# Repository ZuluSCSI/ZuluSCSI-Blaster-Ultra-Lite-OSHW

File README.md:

ZuluSCSI® Blaster Ultra Lite OSHW
================

This repository contains the KiCAD 10 schematic and PCB design files for an Open Source Hardware variant of the RP2350B-based ZuluSCSI® Blaster 

ZuluSCSI® Ultra Lite OSHW is the worlds first* **_open-source**_ [OSHWA-certified](https://certification.oshwa.org/us002873.html) _Ultra_ SCSI emulator, an open-source alternative to our commercially available ZuluSCSI Blaster, designed with cost efficiency in mind.

ZuluSCSI® Blaster Ultra Lite runs unmodified [ZuluSCSI Blaster firmware](https://github.com/ZuluSCSI/ZuluSCSI-firmware/releases)

Pre-prepared gerbers and BoM files are available in [the release section](https://github.com/ZuluSCSI/ZuluSCSI-Blaster-Ultra-Lite-OSHW/releases/tag/Rev2026b)

License
----------------------------

This hardware design is licensed under the terms of the [strongly reciprocal CERN OHL-S V2 license](https://ohwr.org/cern_ohl_s_v2.txt) 

ZuluSCSI® is a registered trademark of Rabbit Hole Computing, and may not be used commercially without the express written consent of Rabbit Hole Computing. Individuals producing ZuluSCSI boards for personal use are hereby granted permission to use the ZuluSCSI trademark in a noncommercial capacity.

_Any_ use of the ZuluSCSI® [registered trademark](https://tmsearch.uspto.gov/search/search-results/97574699) in a **commercial** context requires **prior written consent from Rabbit Hole Computing.**

*That we know of :)

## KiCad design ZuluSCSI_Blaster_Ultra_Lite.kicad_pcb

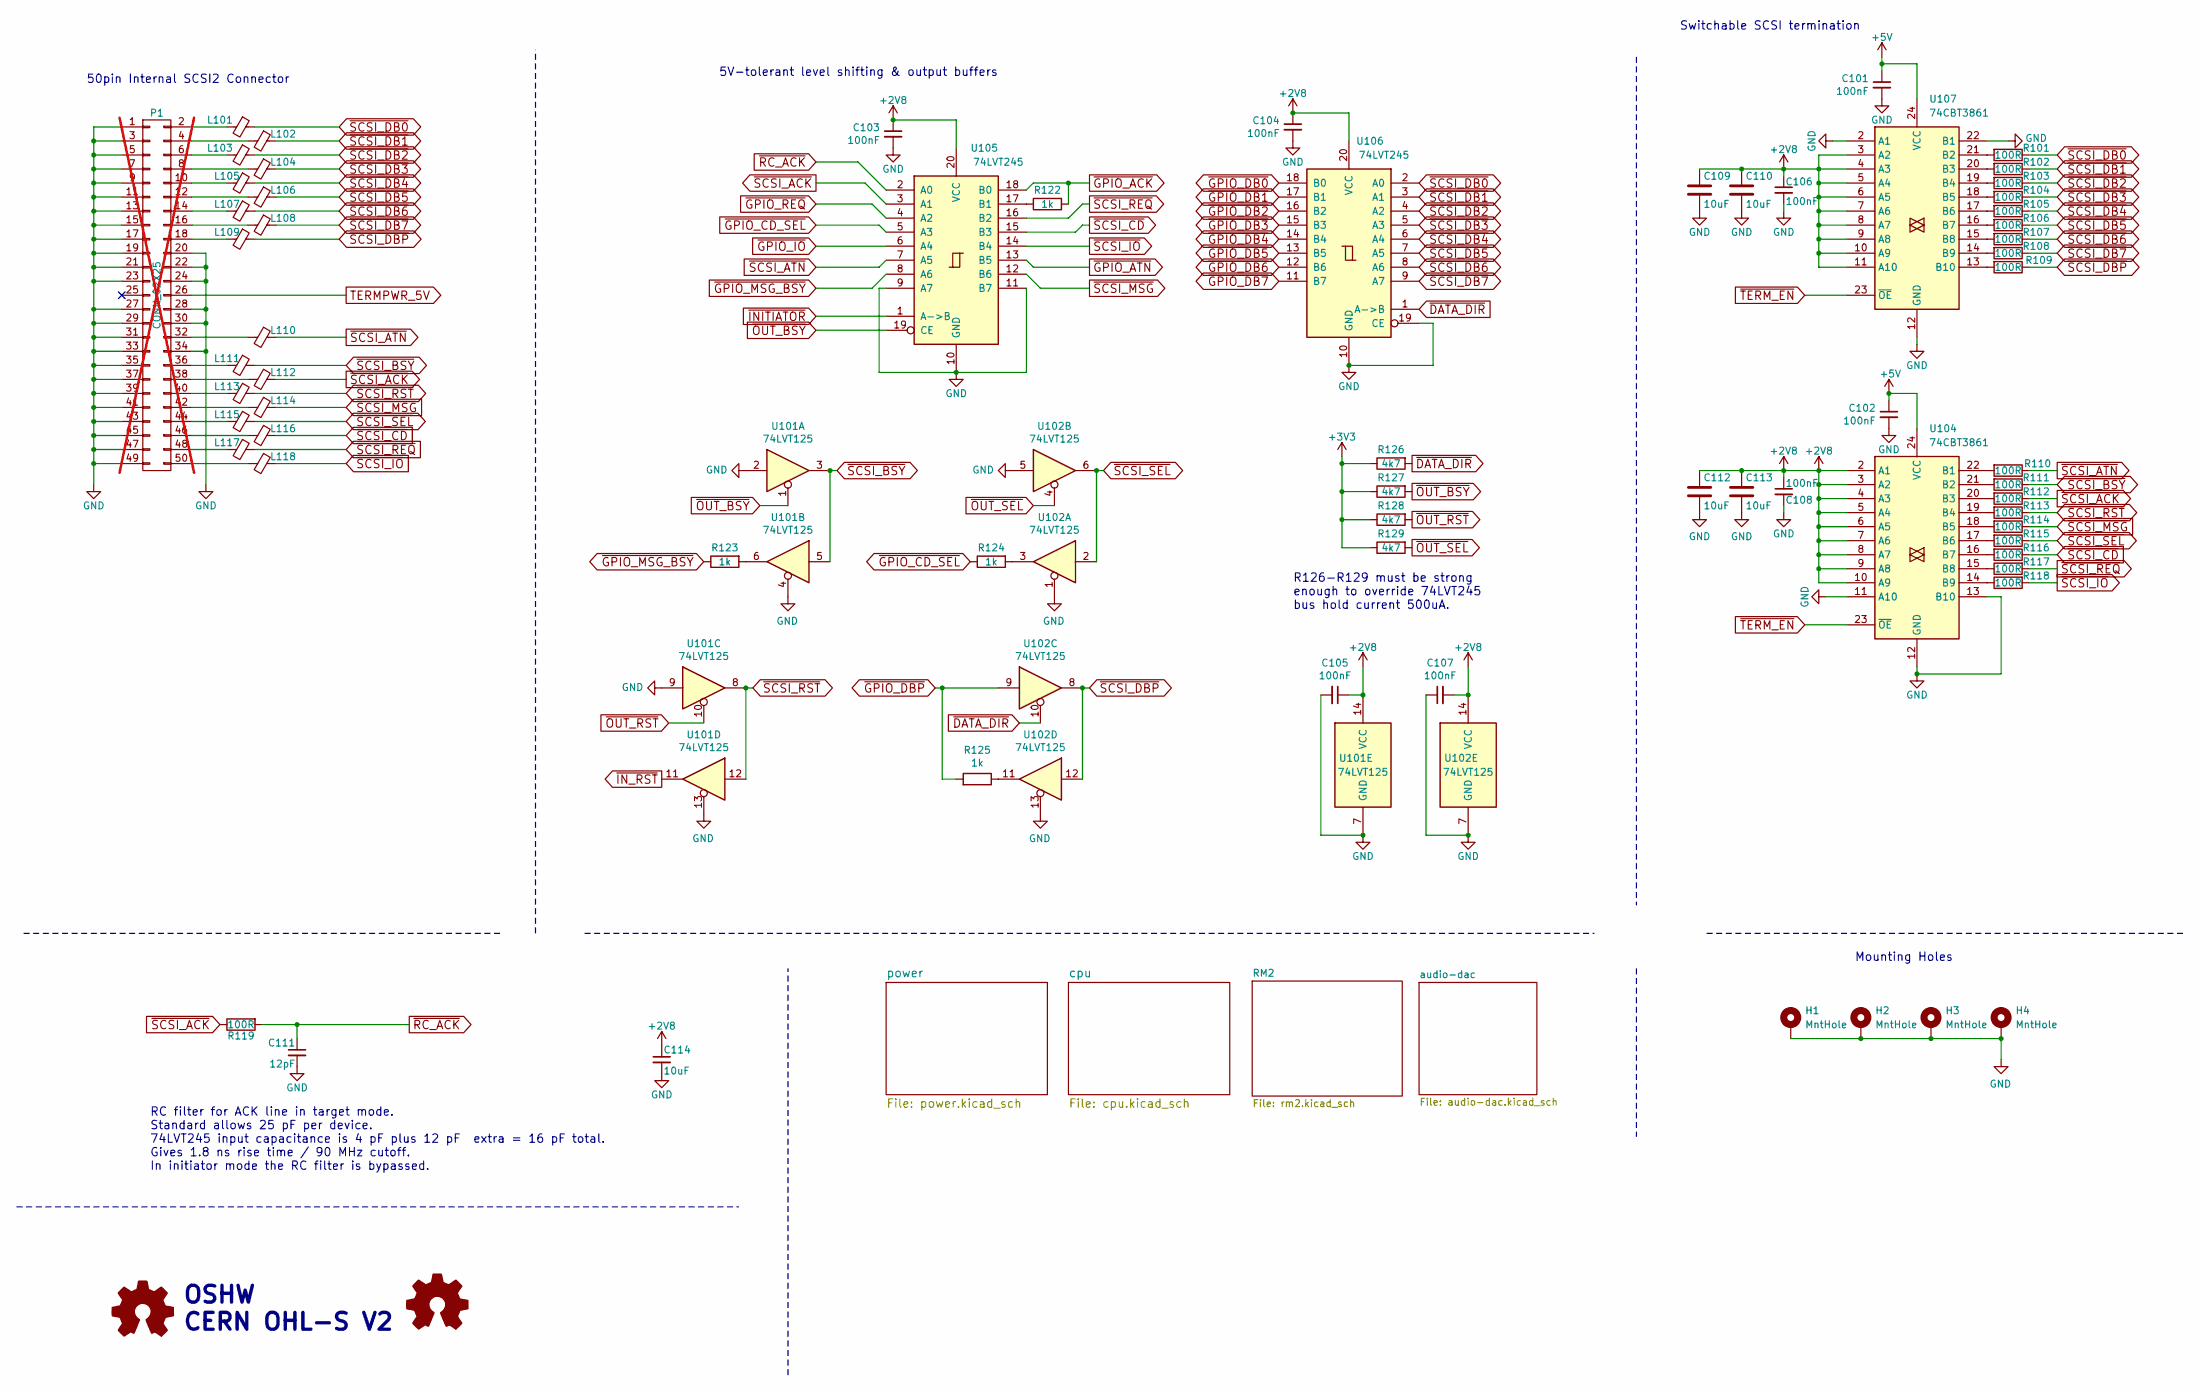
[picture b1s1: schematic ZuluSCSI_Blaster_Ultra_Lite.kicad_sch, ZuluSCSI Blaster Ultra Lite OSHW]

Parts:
C101, C102, C103, C104, C105, C106, C107, C108: 100nF; C_0402_1005Metric; PartNumber CL05B104KO5NNNC; LCSC C1525
C109, C110, C112, C113: 10uF; C_0805_2012Metric; Voltage Rating 16V; PartNumber CL21A106KAYNNNE; LCSC C15850
C111: 12pF; C_0603_1608Metric; PartNumber C0603C120J5GAC7867; LCSC C38523
C114: 10uF; C_0805_2012Metric; PartNumber CL21A106KAYNNNE; LCSC C15850
H1, H2, H3, H4: MntHole; Screw_Hole_M3
L101, L102, L103, L104, L105, L106, L107, L108, L109, L110, L111, L112, L113, L114, L115, L116, L117, L118: Ferrite_Bead_Small; L_0603_1608Metric; PartNumber BLM18PG330SN1D; LCSC C88984
P1: CONN_02X25; IDC-Header_2x25_P2.54mm_Horizontal; PartNumber SBH11-PBPC-D25-RA-BK; LCSC C19193830; not fitted
R101, R102, R103, R104, R105, R106, R107, R108, R109, R110, R111, R112, R113, R114, R115, R116, R117, R118, R119: 100R; R_0603_1608Metric; PartNumber RC0603FR-07100RL; LCSC C22775
R122, R123, R124, R125: 1k; R_0603_1608Metric; PartNumber RC0603JR-071KL; LCSC C21190
R126, R127, R128, R129: 4k7; R_0603_1608Metric; PartNumber RC0603JR-074K7L; LCSC C23162
SYM1, SYM2: Logo_Open_Hardware_Small; OSHW-Logo_5.7x6mm_Copper_SolderMask
U101, U102: 74LVT125; SSOP_TSSOP-14_4.4x5mm_Pitch0.65mm_PCBWay-MaskClearance0.22mm; PartNumber SN74LVT125PWR; LCSC C7042
U104, U107: 74CBT3861; TSSOP-24_4.4x7.8mm_P0.65mm; PartNumber SN74CBT3861PWR; JLCPCBCORRECT 0;0;-90
U105, U106: 74LVT245; SSOP_TSSOP-20_5.3x7.2mm_P0.65mm; PartNumber SN74LVTH245APWR; LCSC C2652121

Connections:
+2V8: C103.1, C104.1, C105.1, C106.1, C107.2, C108.1, C109.1, C110.1, C112.1, C113.1, C114.1, U101.14 (VCC), U102.14 (VCC), U104.2 (A1), U104.3 (A2), U104.4 (A3), U104.5 (A4), U104.6 (A5), U104.7 (A6), U104.8 (A7), U104.9 (A8), U104.10 (A9), U105.20 (VCC), U106.20 (VCC), U107.3 (A2), U107.4 (A3), U107.5 (A4), U107.6 (A5), U107.7 (A6), U107.8 (A7), U107.9 (A8), U107.10 (A9), U107.11 (A10); also elsewhere on the board
+3V3: R126.1, R127.1, R128.1, R129.1; also elsewhere on the board
+5V: C101.1, C102.1, U104.24 (VCC), U107.24 (VCC); also elsewhere on the board
GND: C101.2, C102.2, C103.2, C104.2, C105.2, C106.2, C107.1, C108.2, C109.2, C110.2, C111.2, C112.2, C113.2, C114.2, H1.1 (1_1), H2.1 (1_1), H3.1 (1_1), H4.1 (1_1), P1.1, P1.3, P1.5, P1.7, P1.9, P1.11, P1.13, P1.15, P1.17, P1.19, P1.20, P1.21, P1.22, P1.23, P1.24, P1.27, P1.28, P1.29, P1.30, P1.31, P1.33, P1.34, P1.35, P1.37, P1.39, P1.41, P1.43, P1.45, P1.47, P1.49, U101.2, U101.4, U101.7 (GND), U101.9, U101.13, U102.1, U102.5, U102.7 (GND), U102.13, U104.11 (A10), U104.12 (GND), U104.13 (B10), U105.9 (A7), U105.10 (GND), U105.11 (B7), U106.10 (GND), U106.19 (CE), U107.2 (A1), U107.12 (GND), U107.22 (B1); also elsewhere on the board
unnamed: L101.2, P1.2
unnamed: L102.2, P1.4
unnamed: L103.2, P1.6
unnamed: L104.2, P1.8
unnamed: L105.2, P1.10
unnamed: L106.2, P1.12
unnamed: L107.2, P1.14
unnamed: L108.2, P1.16
unnamed: L109.2, P1.18
unnamed: L110.2, P1.32
unnamed: L111.2, P1.36
unnamed: L112.2, P1.38
unnamed: L113.2, P1.40
unnamed: L114.2, P1.42
unnamed: L115.2, P1.44
unnamed: L116.2, P1.46
unnamed: L117.2, P1.48
unnamed: L118.2, P1.50
unnamed: R123.2, U101.6
unnamed: R124.2, U102.3
unnamed: R125.1, U102.11
unnamed: R110.2, U104.22 (B1)
unnamed: R111.2, U104.21 (B2)
unnamed: R112.2, U104.20 (B3)
unnamed: R113.2, U104.19 (B4)
unnamed: R114.2, U104.18 (B5)
unnamed: R115.2, U104.17 (B6)
unnamed: R116.2, U104.16 (B7)
unnamed: R117.1, U104.15 (B8)
unnamed: R118.1, U104.14 (B9)
unnamed: R122.1, U105.17 (B1)
unnamed: R101.2, U107.21 (B2)
unnamed: R102.2, U107.20 (B3)
unnamed: R103.2, U107.19 (B4)
unnamed: R104.2, U107.18 (B5)
unnamed: R105.2, U107.17 (B6)
unnamed: R106.2, U107.16 (B7)
unnamed: R107.2, U107.15 (B8)
unnamed: R108.2, U107.14 (B9)
unnamed: R109.2, U107.13 (B10)
TERMPWR_5V: P1.26; also elsewhere on the board
~DATA_DIR: R126.2, U102.10, U106.1 (A->B); also elsewhere on the board
~GPIO_ACK: R122.2, U105.18 (B0); also elsewhere on the board
~GPIO_ATN: U105.13 (B5); also elsewhere on the board
~GPIO_CD_SEL: R124.1, U105.5 (A3); also elsewhere on the board
~GPIO_DB0: U106.18 (B0); also elsewhere on the board
~GPIO_DB1: U106.17 (B1); also elsewhere on the board
~GPIO_DB2: U106.16 (B2); also elsewhere on the board
~GPIO_DB3: U106.15 (B3); also elsewhere on the board
~GPIO_DB4: U106.14 (B4); also elsewhere on the board
~GPIO_DB5: U106.13 (B5); also elsewhere on the board
~GPIO_DB6: U106.12 (B6); also elsewhere on the board
~GPIO_DB7: U106.11 (B7); also elsewhere on the board
~GPIO_DBP: R125.2, U102.9; also elsewhere on the board
~GPIO_IO: U105.6 (A4); also elsewhere on the board
~GPIO_MSG_BSY: R123.1, U105.8 (A6); also elsewhere on the board
~GPIO_REQ: U105.4 (A2); also elsewhere on the board
~INITIATOR: U105.1 (A->B); also elsewhere on the board
~IN_RST: U101.11; also elsewhere on the board
~OUT_BSY: R127.2, U101.1, U105.19 (CE); also elsewhere on the board
~OUT_RST: R128.2, U101.10; also elsewhere on the board
~OUT_SEL: R129.2, U102.4; also elsewhere on the board
~RC_ACK: C111.1, R119.2, U105.2 (A0)
~SCSI_ACK: L112.1, R112.1, R119.1, U105.3 (A1)
~SCSI_ATN: L110.1, R110.1, U105.7 (A5)
~SCSI_BSY: L111.1, R111.1, U101.3, U101.5
~SCSI_CD: L116.1, R116.1, U105.15 (B3)
~SCSI_DB0: L101.1, R101.1, U106.2 (A0)
~SCSI_DB1: L102.1, R102.1, U106.3 (A1)
~SCSI_DB2: L103.1, R103.1, U106.4 (A2)
~SCSI_DB3: L104.1, R104.1, U106.5 (A3)
~SCSI_DB4: L105.1, R105.1, U106.6 (A4)
~SCSI_DB5: L106.1, R106.1, U106.7 (A5)
~SCSI_DB6: L107.1, R107.1, U106.8 (A6)
~SCSI_DB7: L108.1, R108.1, U106.9 (A7)
~SCSI_DBP: L109.1, R109.1, U102.8, U102.12
~SCSI_IO: L118.1, R118.2, U105.14 (B4)
~SCSI_MSG: L114.1, R114.1, U105.12 (B6)
~SCSI_REQ: L117.1, R117.2, U105.16 (B2)
~SCSI_RST: L113.1, R113.1, U101.8, U101.12
~SCSI_SEL: L115.1, R115.1, U102.2, U102.6
~TERM_EN: U104.23 (~OE), U107.23 (~OE); also elsewhere on the board

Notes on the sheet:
Switchable SCSI termination
R126-R129 must be strong enough to override 74LVT245 bus hold current 500uA.
5V-tolerant level shifting & output buffers
50pin Internal SCSI2 Connector
Mounting Holes
OSHW CERN OHL-S V2
RC filter for ACK line in target mode. Standard allows 25 pF per device. 74LVT245 input capacitance is 4 pF plus 12 pF extra = 16 pF total. Gives 1.8 ns rise time / 90 MHz cutoff. In initiator mode the RC filter is bypassed.

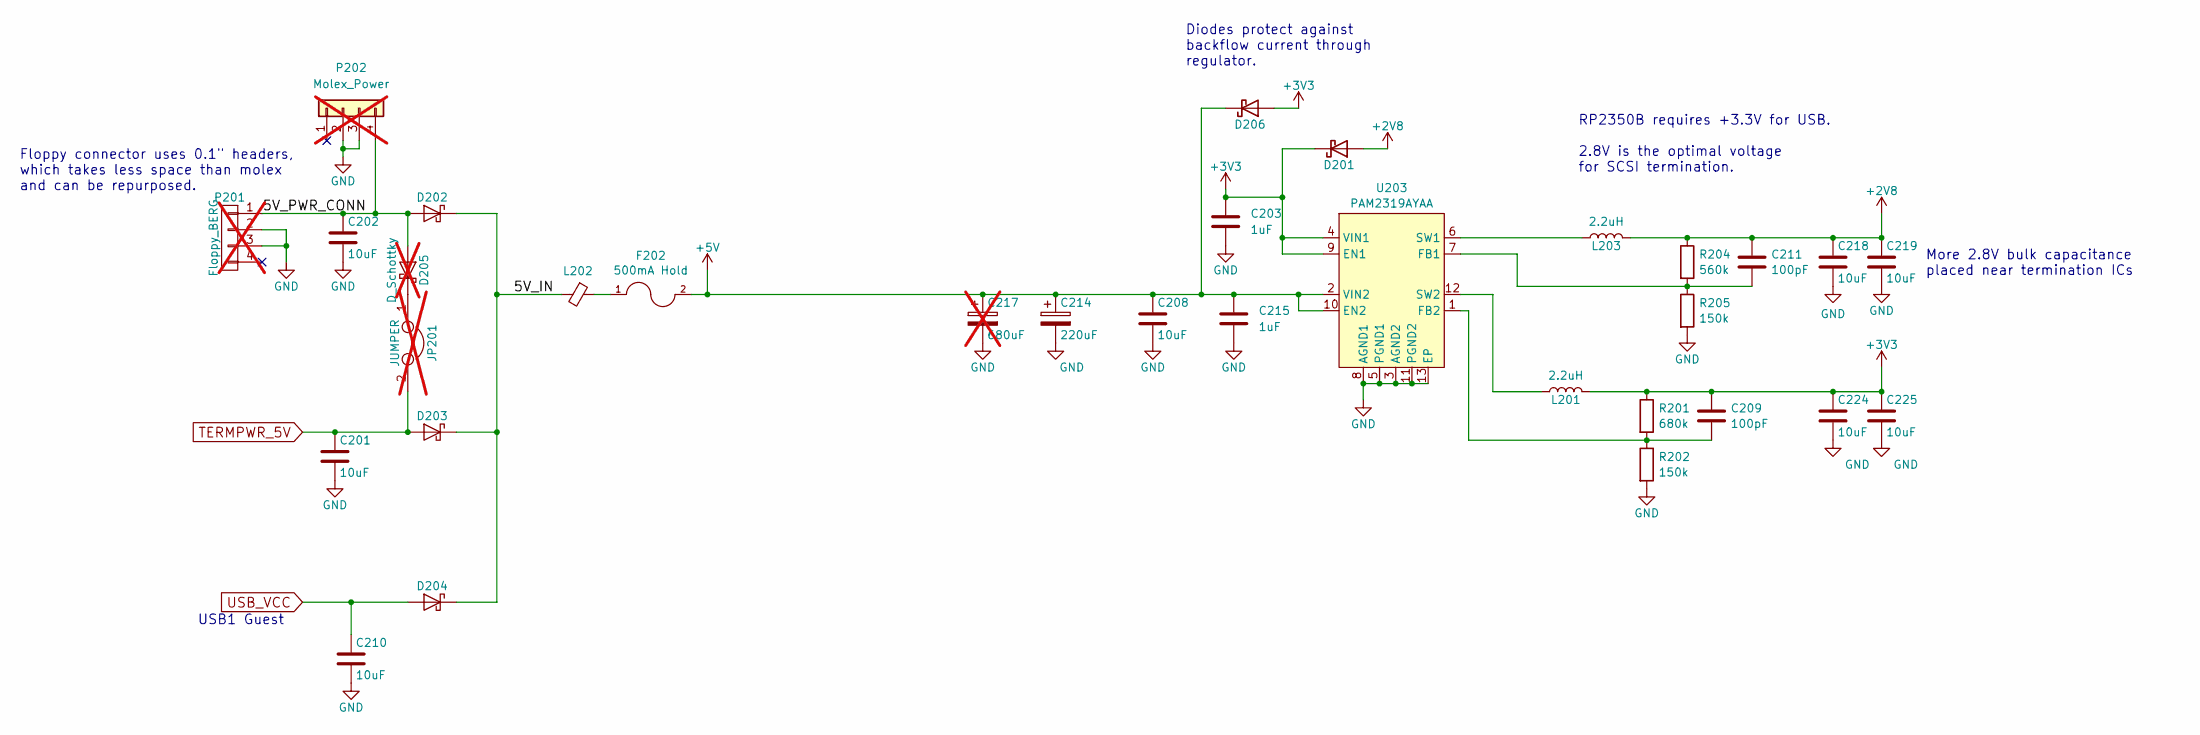
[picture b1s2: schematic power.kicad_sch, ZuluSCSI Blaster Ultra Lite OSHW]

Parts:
C201, C202, C210: 10uF; C_0805_2012Metric; PartNumber CL21A106KAYNNNE; LCSC C15850
C203, C215: 1uF; C_0402_1005Metric; PartNumber CL05A105KA5NQNC; LCSC C52923
C208, C218, C219, C224, C225: 10uF; C_0805_2012Metric; Voltage Rating 16V; PartNumber CL21A106KAYNNNE; LCSC C15850
C209, C211: 100pF; C_0402_1005Metric; PartNumber CC0402JRNPO9BN101; LCSC C106200
C214: 220uF; CP_Elec_6.3x7.7; PartNumber UUD1C221MCL1GS; LCSC C2887273
C217: 680uF; CP_Radial_D8.0mm_P3.50mm; Voltage Rating 10V; PartNumber EEUFR1A681; LCSC N/A; not fitted
D201, D202, D203, D204, D206: D_Schottky; D_SOD-123; PartNumber MBRX120LF-TP; LCSC C8598
D205: D_Schottky; D_SOD-123; PartNumber MBRX120LF-TP; LCSC C8598; not fitted
F202: 500mA Hold; Fuse_1206_3216Metric; PartNumber 0ZCJ0050FF2G; LCSC C43379
JP201: JUMPER; PinHeader_1x02_P2.54mm_Vertical; LCSC N/A; not fitted
L201, L203: 2.2uH; Inductor_1008; PartNumber DFE252012P-2R2M=P2; LCSC C86092
L202: Ferrite_Bead_Small; L_0603_1608Metric; PartNumber BLM18PG330SN1D; LCSC C88984
P201: Floppy_BERG; floppy-berg; PartNumber 171826-4; digikey A112643-ND; not fitted
P202: Molex_Power; molex-vert-TE_350424-1; PartNumber 350211-1; JLCPCB_IGNORE do not fit; not fitted
R201: 680k; R_0402_1005Metric; PartNumber RC0402FR-07680KL; LCSC C4131
R202, R205: 150k; R_0402_1005Metric; PartNumber RMCF0402FT150K; LCSC C93947
R204: 560k; R_0402_1005Metric; PartNumber RC0402FR-07560KL; LCSC C132339
U203: PAM2319AYAA; WDFN-12-1EP_3x3mm_P0.45mm_EP1.7x2.5mm; PartNumber PAM2319AYAA; LCSC C2071057

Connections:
+2V8: C211.1, C218.1, C219.1, D201.2 (A), L203.2, R204.1; also elsewhere on the board
+3V3: C203.1, C209.1, C224.1, C225.1, D201.1 (K), D206.2 (A), L201.2, R201.1, U203.4 (VIN1), U203.9 (EN1); also elsewhere on the board
+5V: C208.1, C214.1, C215.1, C217.1, D206.1 (K), F202.2, U203.2 (VIN2), U203.10 (EN2); also elsewhere on the board
/power/5V_IN: D202.1 (K), D203.1 (K), D204.1 (K), L202.2
/power/5V_PWR_CONN: C202.1, D202.2 (A), D205.2 (A), P201.1, P202.4
GND: C201.2, C202.2, C203.2, C208.2, C210.2, C214.2, C215.2, C217.2, C218.2, C219.2, C224.2, C225.2, P201.2, P201.3, P202.2, P202.3, R202.2, R205.2, U203.3 (AGND2), U203.5 (PGND1), U203.8 (AGND1), U203.11 (PGND2), U203.13 (EP); also elsewhere on the board
unnamed: D205.1 (K), JP201.1
unnamed: F202.1, L202.1
unnamed: C211.2, R204.2, R205.1, U203.7 (FB1)
unnamed: C209.2, R201.2, R202.1, U203.1 (FB2)
unnamed: L203.1, U203.6 (SW1)
unnamed: L201.1, U203.12 (SW2)
TERMPWR_5V: C201.1, D203.2 (A), JP201.2; also elsewhere on the board
USB_VCC: C210.1, D204.2 (A); also elsewhere on the board

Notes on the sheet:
More 2.8V bulk capacitance placed near termination ICs
RP2350B requires +3.3V for USB. 2.8V is the optimal voltage for SCSI termination.
Floppy connector uses 0.1" headers, which takes less space than molex and can be repurposed.
USB1 Guest
Diodes protect against backflow current through regulator.

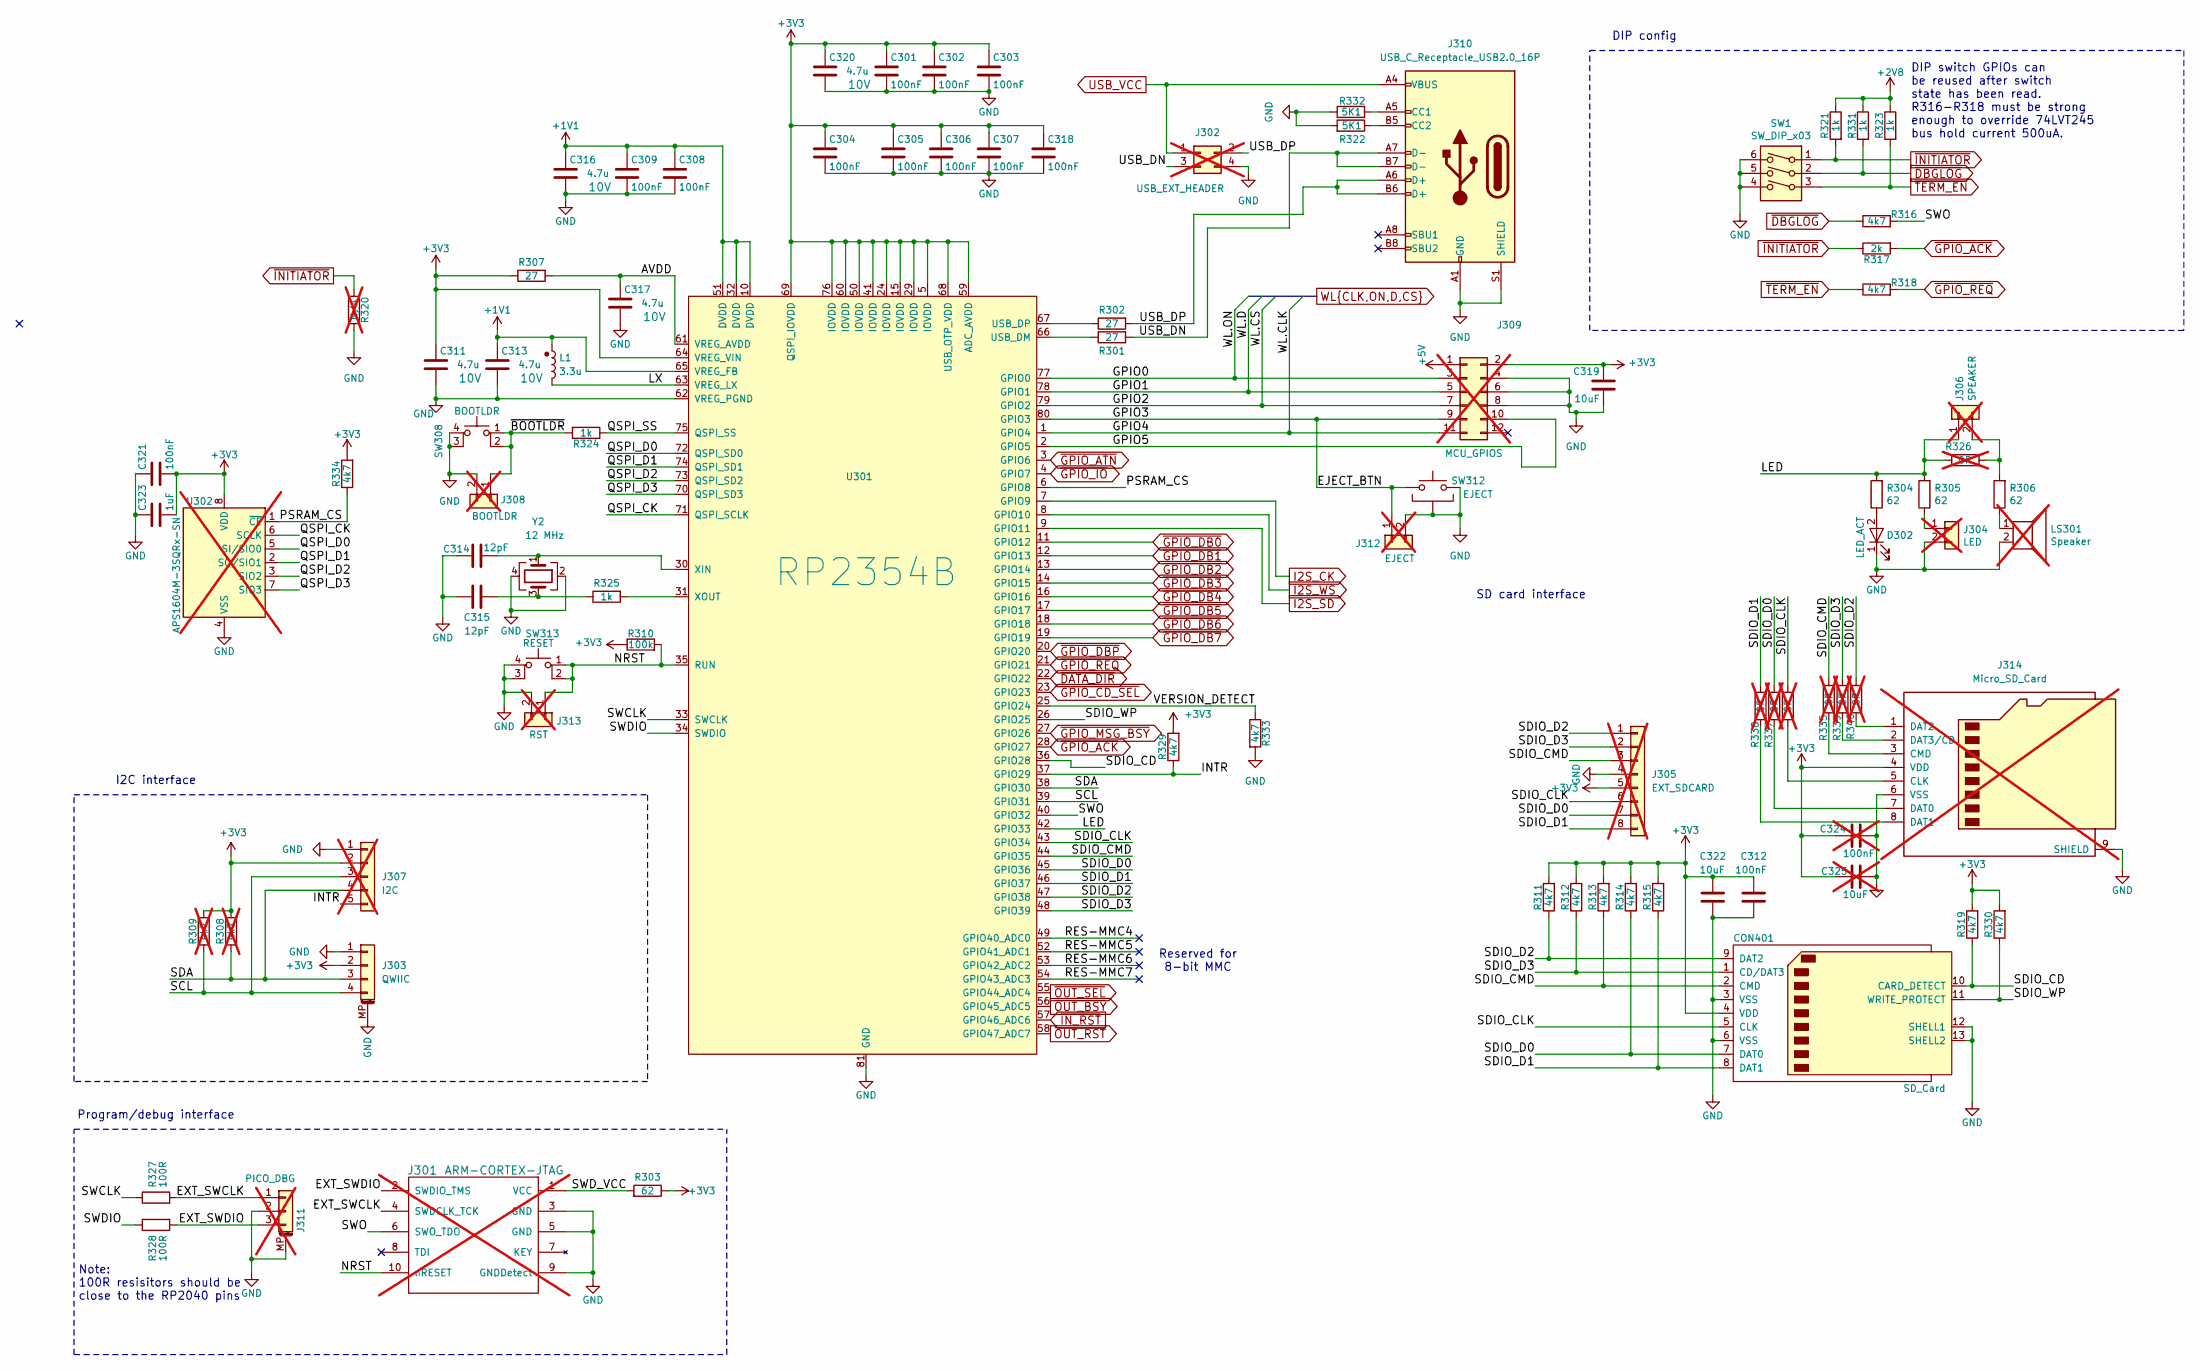
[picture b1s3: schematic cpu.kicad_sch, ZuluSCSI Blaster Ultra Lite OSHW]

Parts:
C301, C302, C303, C304, C305, C306, C307, C308, C309, C312, C318, C321: 100nF; C_0402_1005Metric; PartNumber CL05B104KO5NNNC; LCSC C1525
C311, C313: 4.7u; C_0402_1005Metric_small_pads; Voltage 10V; PartNumber GRM155R61A475MEAAD; LCSC C335105
C314, C315: 12pF; C_0402_1005Metric; PartNumber GCQ1555C1H120GB01D; LCSC C2235030
C316, C317, C320: 4.7u; C_0402_1005Metric; Voltage 10V; PartNumber GRM155R61A475MEAAD; LCSC C335105
C319, C322: 10uF; C_0805_2012Metric; PartNumber CL21A106KAYNNNE; LCSC C15850
C323: 1uF; C_0603_1608Metric; PartNumber UMK107BJ105KA-T; LCSC C15849
C324: 100nF; C_0603_1608Metric; PartNumber CL10B104KB8NNWC; LCSC C14663; not fitted
C325: 10uF; C_0805_2012Metric; PartNumber CL21B106KOQNNNE; LCSC C95841; not fitted
CON401: SD_Card; SD-SMD_SD-101; PartNumber SD-101; LCSC C266601
D302: LED_ACT; LED_0805_2012Metric; LCSC C434435
J301: ARM-CORTEX-JTAG; SAMTEC_FTSH-105-01-LM-D-K; LCSC N/A; not fitted
J302: USB_EXT_HEADER; PinHeader_2x02_P2.54mm_Vertical; JLCPCB_IGNORE do not fit; not fitted
J303: QWIIC; JST_SH_BM04B-SRSS-TB_1x04-1MP_P1.00mm_Vertical; LCSC C160390
J304: LED; PinHeader_1x02_P2.54mm_Vertical; LCSC N/A; not fitted
J305: EXT_SDCARD; PinHeader_1x08_P2.54mm_Vertical; JLCPCB_IGNORE do not fit; not fitted
J306: SPEAKER; PinHeader_1x02_P2.54mm_Vertical; LCSC N/A; not fitted
J307: I2C; PinHeader_1x05_P2.54mm_Vertical; JLCPCB_IGNORE do not fit; not fitted
J308: BOOTLDR; PinHeader_1x02_P2.54mm_Vertical; LCSC N/A; not fitted
J309: MCU_GPIOS; PinSocket_2x06_P2.54mm_Vertical; JLCPCB_IGNORE do not fit; not fitted
J310: USB_C_Receptacle_USB2.0_16P; USB-C-SMD_SHOU_TYPE-C-16P-CB1.6; LCSC C2906290
J311: PICO_DBG; JST_SH_BM03B-SRSS-TB_1x03-1MP_P1.00mm_Vertical; LCSC C160389; not fitted
J312: EJECT; PinHeader_1x02_P2.54mm_Vertical; LCSC N/A; not fitted
J313: RST; PinHeader_1x02_P2.54mm_Vertical; LCSC N/A; not fitted
J314: Micro_SD_Card; SD_FLIP_CONN_47219-2001_MOL; PartNumber 472192001; LCSC C164170; not fitted
L1: 3.3u; L_pol_2016; PartNumber AOTA-B201610S3R3-101-T; digikey 535-AOTA-B201610S3R3-101-TTR-ND
LS301: Speaker; PinHeader_1x02_P2.54mm_Vertical; LCSC N/A; not fitted
R301, R302, R307: 27; R_0402_1005Metric; PartNumber RC0402FR-0727RL; LCSC C138021
R303, R304, R305, R306: 62; R_0603_1608Metric; PartNumber RC0603FR-0762RL; LCSC C25252
R308, R309: 4k7; R_0603_1608Metric; PartNumber RC0603JR-074K7L; LCSC C23162; not fitted
R310: 100k; R_0603_1608Metric; PartNumber RC0603FR-07100KL; LCSC C25803
R311, R312, R313, R314, R315, R316, R318, R319, R329, R330, R333, R334: 4k7; R_0603_1608Metric; PartNumber RC0603JR-074K7L; LCSC C23162
R317: 2k; R_0603_1608Metric; PartNumber RC0603FR-072KL; LCSC C22975
R320: N/A; R_0402_1005Metric; LCSC N/A; not fitted
R321, R323, R324, R331: 1k; R_0603_1608Metric; PartNumber RC0603JR-071KL; LCSC C21190
R322, R332: 5K1; R_0603_1608Metric; LCSC C23186
R325: 1k; R_0402_1005Metric; PartNumber RC0402FR-071KL; LCSC C106235
R326: 0R; R_0603_1608Metric; LCSC N/A; not fitted
R327, R328: 100R; R_0603_1608Metric; PartNumber RC0603FR-07100RL; LCSC C22775
R335, R336, R337, R338, R339, R340: 0R; R_0603_1608Metric; PartNumber RC0603FR-070RL; LCSC C21189; not fitted
SW1: SW_DIP_x03; SW_DIP_SPSTx03_Slide_6.7x9.18mm_W8.61mm_P2.54mm_LowProfile; PartNumber 219-3MSTR; LCSC C319040
SW308: BOOTLDR; SW-SMD_4P-L5.1-W5.1-P3.70-LS6.5-TL_H1.5; PartNumber PTS526SM15SMTR2 LFS; LCSC C318884
SW312: EJECT; SW-SMD_GT-TC108A-H034-L1S; LCSC C22396279
SW313: RESET; SW-SMD_4P-L5.1-W5.1-P3.70-LS6.5-TL_H1.5; PartNumber PTS526SM15SMTR2 LFS; LCSC C318884
U301: RP2354B; QFN-80-1EP_10x10mm_P0.4mm_EP3.4x3.4mm_ThermalVias; PartNumber RP2354B; LCSC C39843328
U302: APS1604M-3SQRx-SN; SOIC-8_3.9x4.9mm_P1.27mm; PartNumber APS1604M-3SQR-SN; LCSC C18214056; not fitted
Y2: 12 MHz; Crystal_SMD_3225-4Pin_3.2x2.5mm; PartNumber ABM8-272-T3; LCSC C20625731

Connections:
+1V1: C308.1, C309.1, C313.1, C316.1, L1.1, U301.10 (DVDD), U301.32 (DVDD), U301.51 (DVDD), U301.65 (VREG_FB)
+2V8: R321.1, R323.1, R331.1; also elsewhere on the board
+3V3: C301.1, C302.1, C303.1, C304.1, C305.1, C306.1, C307.1, C311.1, C312.2, C318.1, C319.1, C320.1, C321.2, C322.2, C323.2, C324.2, C325.2, CON401.4 (VDD), J303.2, J305.5, J307.2, J309.2, J314.4 (VDD), R303.1, R307.1, R308.2, R309.2, R310.1, R311.2, R312.2, R313.2, R314.2, R315.2, R319.2, R329.2, R330.2, R334.2, U301.5 (IOVDD), U301.15 (IOVDD), U301.24 (IOVDD), U301.29 (IOVDD), U301.41 (IOVDD), U301.50 (IOVDD), U301.59 (ADC_AVDD), U301.60 (IOVDD), U301.64 (VREG_VIN), U301.68 (USB_OTP_VDD), U301.69 (QSPI_IOVDD), U301.76 (IOVDD), U302.8 (VDD); also elsewhere on the board
+5V: J309.1; also elsewhere on the board
/cpu/AVDD: C317.1, R307.2, U301.61 (VREG_AVDD)
/cpu/EJECT_BTN: J309.9, J312.1, SW312.2, U301.80 (GPIO3)
/cpu/EXT_SWCLK: J301.4 (SWDCLK_TCK), J311.1, R327.2
/cpu/EXT_SWDIO: J301.2 (SWDIO_TMS), J311.3, R328.2
/cpu/GPIO5: J309.10, U301.2 (GPIO5)
/cpu/INTR: J307.5, R329.1, U301.37 (GPIO29)
/cpu/LED: J306.1, R304.2, R305.2, R326.2, U301.42 (GPIO33)
/cpu/LX: L1.2, U301.63 (VREG_LX)
/cpu/NRST: J301.10 (nRESET), J313.1, R310.2, SW313.1, SW313.2, U301.35 (RUN)
/cpu/PSRAM_CS: R334.1, U301.6 (GPIO8), U302.1 (~CE)
/cpu/QSPI_CK: U301.71 (QSPI_SCLK), U302.6 (SCLK)
/cpu/QSPI_D0: U301.72 (QSPI_SD0), U302.5 (SI/SIO0)
/cpu/QSPI_D1: U301.74 (QSPI_SD1), U302.2 (SO/SIO1)
/cpu/QSPI_D2: U301.73 (QSPI_SD2), U302.3 (SIO2)
/cpu/QSPI_D3: U301.70 (QSPI_SD3), U302.7 (SIO3)
/cpu/QSPI_SS: R324.1, U301.75 (QSPI_SS)
/cpu/RES-MMC4: U301.49 (GPIO40_ADC0)
/cpu/RES-MMC5: U301.52 (GPIO41_ADC1)
/cpu/RES-MMC6: U301.53 (GPIO42_ADC2)
/cpu/RES-MMC7: U301.54 (GPIO43_ADC3)
/cpu/SCL: J303.4, J307.3, R309.1, U301.39 (GPIO31)
/cpu/SDA: J303.3, J307.4, R308.1, U301.38 (GPIO30)
/cpu/SDIO_CD: CON401.10 (CARD_DETECT), R319.1, U301.36 (GPIO28)
/cpu/SDIO_CLK: CON401.5 (CLK), J305.6, R336.2, U301.43 (GPIO34)
/cpu/SDIO_CMD: CON401.2 (CMD), J305.3, R313.1, R335.2, U301.44 (GPIO35)
/cpu/SDIO_D0: CON401.7 (DAT0), J305.7, R314.1, R337.2, U301.45 (GPIO36)
/cpu/SDIO_D1: CON401.8 (DAT1), J305.8, R315.1, R338.2, U301.46 (GPIO37)
/cpu/SDIO_D2: CON401.9 (DAT2), J305.1, R311.1, R340.2, U301.47 (GPIO38)
/cpu/SDIO_D3: CON401.1 (CD/DAT3), J305.2, R312.1, R339.2, U301.48 (GPIO39)
/cpu/SDIO_WP: CON401.11 (WRITE_PROTECT), R330.1, U301.26 (GPIO25)
/cpu/SWCLK: R327.1, U301.33 (SWCLK)
/cpu/SWDIO: R328.1, U301.34 (SWDIO)
/cpu/SWD_VCC: J301.1 (VCC), R303.2
/cpu/SWO: J301.6 (SWO_TDO), R316.2, U301.40 (GPIO32)
/cpu/USB_DN: J302.3, J310.A7 (D-), J310.B7 (D-), R301.2
/cpu/USB_DP: J302.2, J310.A6 (D+), J310.B6 (D+), R302.2
/cpu/VERSION_DETECT: R333.1, U301.25 (GPIO24)
/cpu/~BOOTLDR: J308.1, R324.2, SW308.1, SW308.2
GND: C301.2, C302.2, C303.2, C304.2, C305.2, C306.2, C307.2, C308.2, C309.2, C311.2, C312.1, C313.2, C314.2, C315.2, C316.2, C317.2, C318.2, C319.2, C320.2, C321.1, C322.1, C323.1, C324.1, C325.1, CON401.3 (VSS), CON401.6 (VSS), CON401.12 (SHELL1), CON401.13 (SHELL2), D302.1 (K), J301.3 (GND), J301.5 (GND), J301.9 (GNDDetect), J302.4, J303.1, J303.MP (MountPin), J304.2, J305.4, J307.1, J308.2, J309.4, J309.6, J309.8, J310.A1 (GND), J310.A12 (GND), J310.B1 (GND), J310.B12 (GND), J310.S1 (SHIELD), J311.2, J311.MP (MountPin), J312.2, J313.2, J314.6 (VSS), J314.9 (SHIELD), LS301.2, R320.2, R322.2, R332.1, R333.2, SW1.4, SW1.5, SW1.6, SW308.3 (K), SW308.4 (A), SW312.1, SW312.3 (MNT), SW313.3 (K), SW313.4 (A), U301.62 (VREG_PGND), U301.81 (GND), U302.4 (VSS), Y2.2, Y2.4; also elsewhere on the board
I2S_CK: U301.7 (GPIO9); also elsewhere on the board
I2S_SD: U301.9 (GPIO11); also elsewhere on the board
I2S_WS: U301.8 (GPIO10); also elsewhere on the board
unnamed: C315.1, R325.1, Y2.3
unnamed: D302.2 (A), R304.1
unnamed: J304.1, R305.1
unnamed: J306.2, R306.2, R326.1
unnamed: J310.A5 (CC1), R332.2
unnamed: J310.B5 (CC2), R322.1
unnamed: J314.5 (CLK), R336.1
unnamed: J314.3 (CMD), R335.1
unnamed: J314.7 (DAT0), R337.1
unnamed: J314.8 (DAT1), R338.1
unnamed: J314.1 (DAT2), R340.1
unnamed: J314.2 (DAT3/CD), R339.1
unnamed: LS301.1, R306.1
unnamed: R301.1, U301.66 (USB_DM)
unnamed: R302.1, U301.67 (USB_DP)
unnamed: C314.1, U301.30 (XIN), Y2.1
unnamed: R325.2, U301.31 (XOUT)
USB_VCC: J302.1, J310.A4 (VBUS), J310.A9 (VBUS), J310.B4 (VBUS), J310.B9 (VBUS); also elsewhere on the board
WL.CLK: J309.11, U301.1 (GPIO4); also elsewhere on the board
WL.CS: J309.7, U301.79 (GPIO2); also elsewhere on the board
WL.D: J309.5, U301.78 (GPIO1); also elsewhere on the board
WL.ON: J309.3, U301.77 (GPIO0); also elsewhere on the board
~DATA_DIR: U301.22 (GPIO22); also elsewhere on the board
~DBGLOG: R316.1, R331.2, SW1.2
~GPIO_ACK: R317.2, U301.28 (GPIO27); also elsewhere on the board
~GPIO_ATN: U301.3 (GPIO6); also elsewhere on the board
~GPIO_CD_SEL: U301.23 (GPIO23); also elsewhere on the board
~GPIO_DB0: U301.11 (GPIO12); also elsewhere on the board
~GPIO_DB1: U301.12 (GPIO13); also elsewhere on the board
~GPIO_DB2: U301.13 (GPIO14); also elsewhere on the board
~GPIO_DB3: U301.14 (GPIO15); also elsewhere on the board
~GPIO_DB4: U301.16 (GPIO16); also elsewhere on the board
~GPIO_DB5: U301.17 (GPIO17); also elsewhere on the board
~GPIO_DB6: U301.18 (GPIO18); also elsewhere on the board
~GPIO_DB7: U301.19 (GPIO19); also elsewhere on the board
~GPIO_DBP: U301.20 (GPIO20); also elsewhere on the board
~GPIO_IO: U301.4 (GPIO7); also elsewhere on the board
~GPIO_MSG_BSY: U301.27 (GPIO26); also elsewhere on the board
~GPIO_REQ: R318.2, U301.21 (GPIO21); also elsewhere on the board
~INITIATOR: R317.1, R320.1, R321.2, SW1.1; also elsewhere on the board
~IN_RST: U301.57 (GPIO46_ADC6); also elsewhere on the board
~OUT_BSY: U301.56 (GPIO45_ADC5); also elsewhere on the board
~OUT_RST: U301.58 (GPIO47_ADC7); also elsewhere on the board
~OUT_SEL: U301.55 (GPIO44_ADC4); also elsewhere on the board
~TERM_EN: R318.1, R323.2, SW1.3; also elsewhere on the board

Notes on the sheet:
Program/debug interface
Reserved for 8-bit MMC
DIP config
Note: 100R resisitors should be close to the RP2040 pins
SD card interface
I2C interface
DIP switch GPIOs can be reused after switch state has been read. R316-R318 must be strong enough to override 74LVT245 bus hold current 500uA.

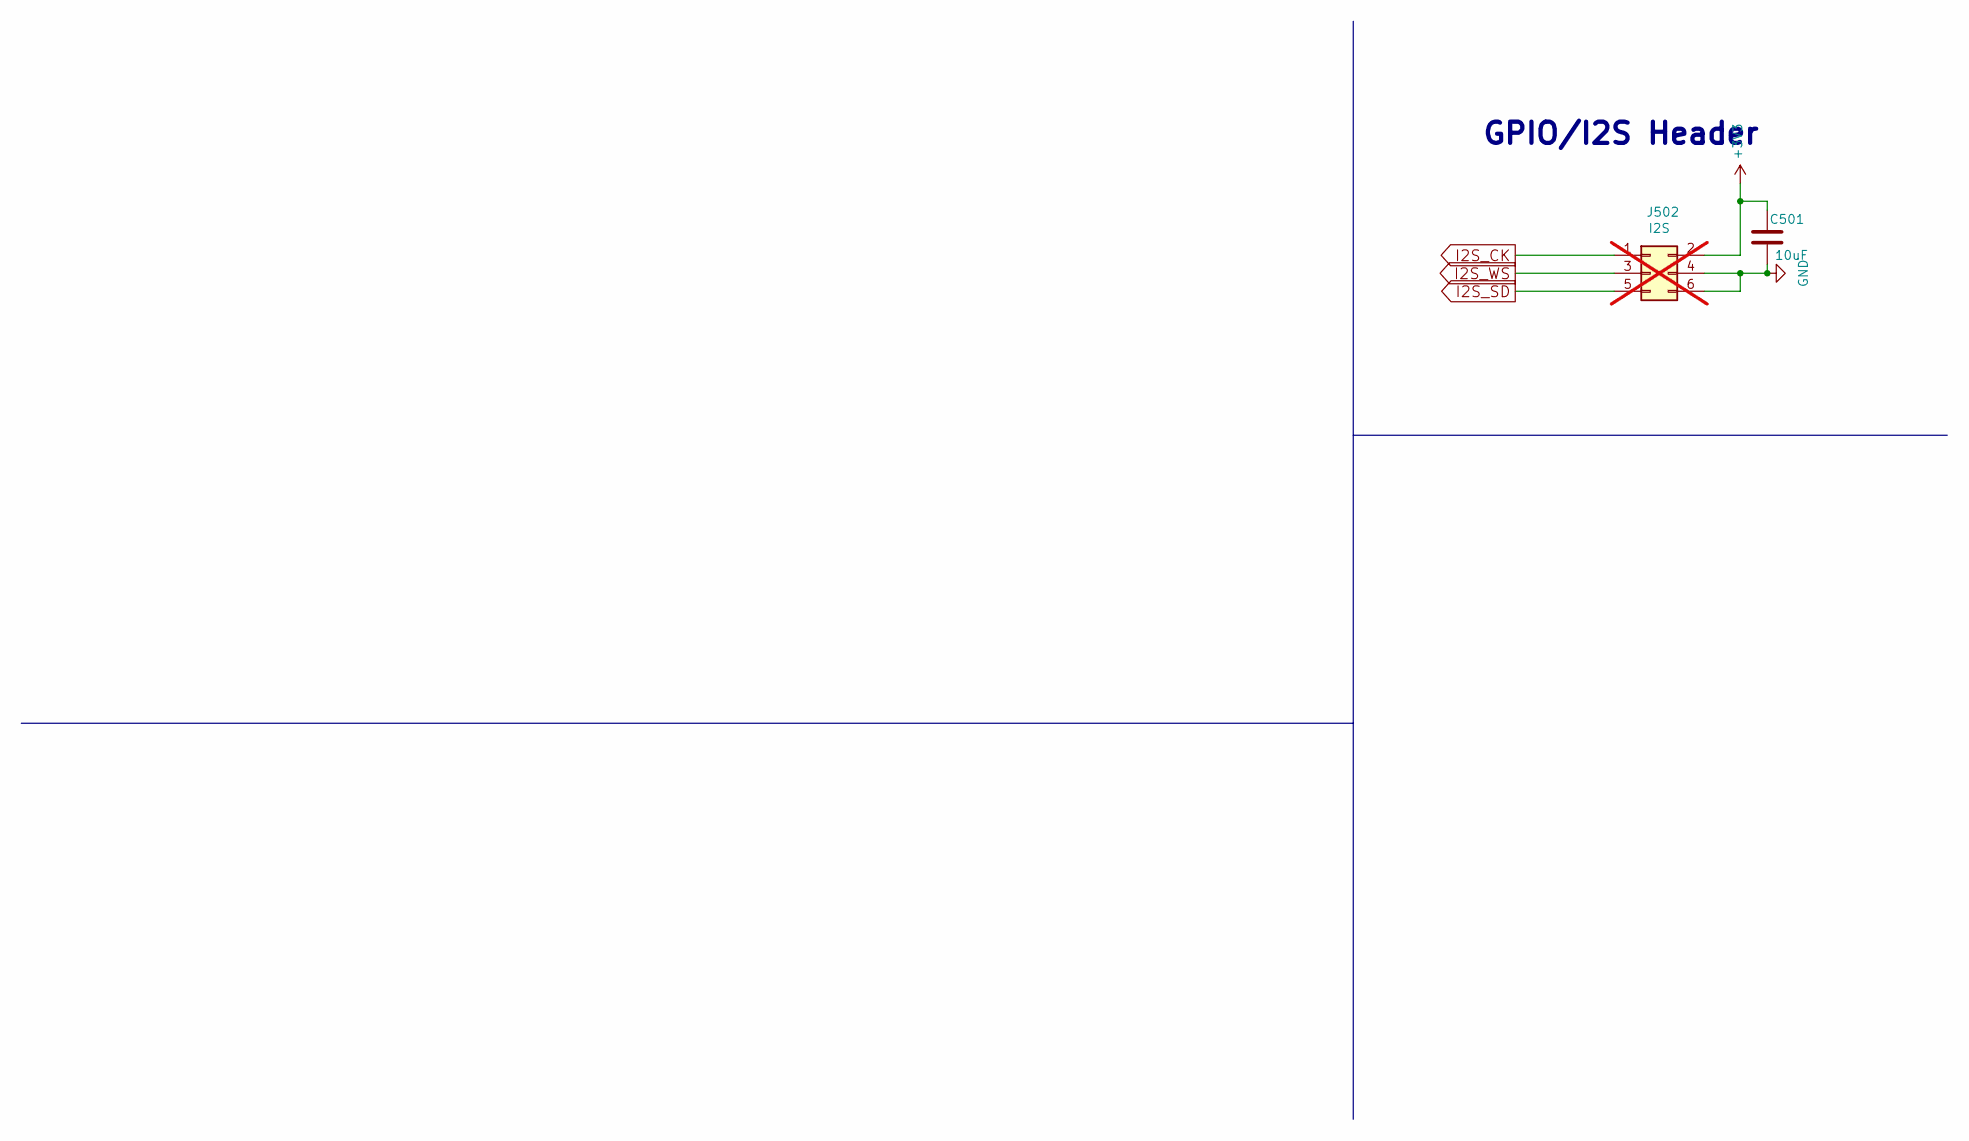
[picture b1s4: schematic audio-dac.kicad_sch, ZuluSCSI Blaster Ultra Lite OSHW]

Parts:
C501: 10uF; C_0805_2012Metric; PartNumber CL21A106KAYNNNE; LCSC C15850
J502: I2S; PinHeader_2x03_P2.54mm_Vertical; JLCPCB_IGNORE do not fit; not fitted

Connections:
+3V3: C501.1, J502.2; also elsewhere on the board
GND: C501.2, J502.4, J502.6; also elsewhere on the board
I2S_CK: J502.1; also elsewhere on the board
I2S_SD: J502.5; also elsewhere on the board
I2S_WS: J502.3; also elsewhere on the board

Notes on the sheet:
GPIO/I2S Header

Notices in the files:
ZuluSCSI_Blaster_Ultra_Lite.kicad_sch:
Copyright 2026 Rabbit Hole Computing
Licensed under CERN OHL-S V2
parts and their libraries:
Copyright: ©2026 Rabbit Hole Computing LLC
